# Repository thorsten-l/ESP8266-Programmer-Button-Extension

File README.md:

# ESP8266-Programmer-Button-Extension

A very simple RESET and GPIO0 button extension board for a ESP8266 USB programmer

Nowadays you can buy handy little USB programmer board for the ESP8266-01 and they are cheap (very very cheap in China).

- [aliexpress](https://www.aliexpress.com/af/ch340-usb-to-esp8266-esp-01.html?g=y&SearchText=ch340+usb+to+esp8266+esp+01&d=y&misspellText=ch340+usb+to+esp8266+esp+01&initiative_id=SC_20190127060118&origin=n&spm=2114.search0604.spellresult.1.5f7e6e9b2Ri52a&isViewCP=y&jump=afs)
- [amazon.com](https://www.amazon.com/s/ref=a9_asi_1?rh=i%3Aaps%2Ck%3Ach340+usb+to+esp8266+esp01&keywords=ch340+usb+to+esp8266+esp01&ie=UTF8&qid=1548597881)
- [amazon.de](https://www.amazon.de/s/ref=a9_asc_1?rh=i%3Aaps%2Ck%3Ach340+usb+to+esp8266+esp+01&keywords=ch340+usb+to+esp8266+esp+01&ie=UTF8&qid=1548597795)

The only anoying thing is they have no RESET or PROGRAMMING (GPIO0) buttons.
But this is easily to solve, because the pins of the yellow socket are quite long and you can solder your own button board under the programmer board.

You have to solder the two buttons and three wires only and you are ready :-)

The right button is the PROGRAMMING (GPIO0) button the left one is the RESET button. The best way to put your ESP in programming mode is to use one finger press down the PROGRAMMING button and with the same finger press down the RESET button. Release the buttons first RESET than PROGRAMMING and your ESP is in programming mode.

If your serial monitor speed is set to 74880 you will see this message:

`ets Jan  8 2013,rst cause:2, boot mode:(1,6)`

boot mode (1,x) means programming mode

boot mode (3,x) is the running mode

## Program

The board files are created with [KiCad EDA](http://kicad-pcb.org/).

---

Have fun with this very tiny hack.

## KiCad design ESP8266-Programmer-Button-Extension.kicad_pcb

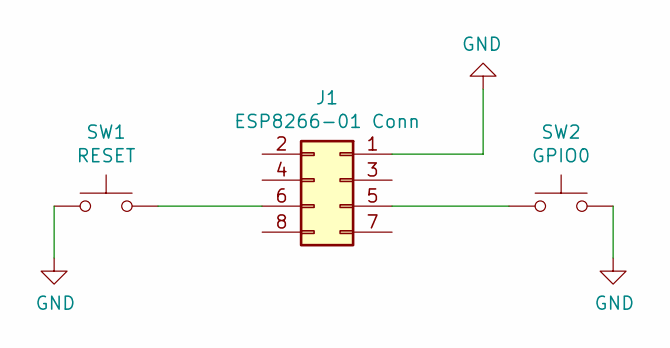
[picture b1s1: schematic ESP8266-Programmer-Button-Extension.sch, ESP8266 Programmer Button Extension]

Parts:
J1: ESP8266-01 Conn; PinSocket_2x04_P2.54mm_Vertical
SW1: RESET; SW_PUSH_6mm
SW2: GPIO0; SW_PUSH_6mm

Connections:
GND: J1.1, SW1.1, SW2.1
unnamed: J1.5, SW2.2
unnamed: J1.6, SW1.2

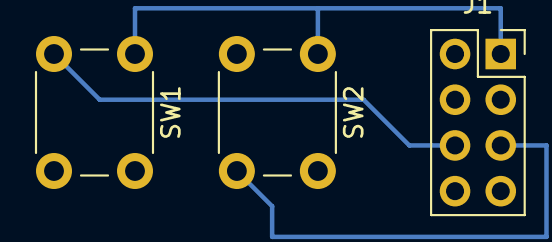
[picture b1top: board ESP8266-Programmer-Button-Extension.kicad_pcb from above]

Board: 2 copper layers, 3 parts (0 on the bottom side), 3 nets.

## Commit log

2019-01-27 KiCad link added
